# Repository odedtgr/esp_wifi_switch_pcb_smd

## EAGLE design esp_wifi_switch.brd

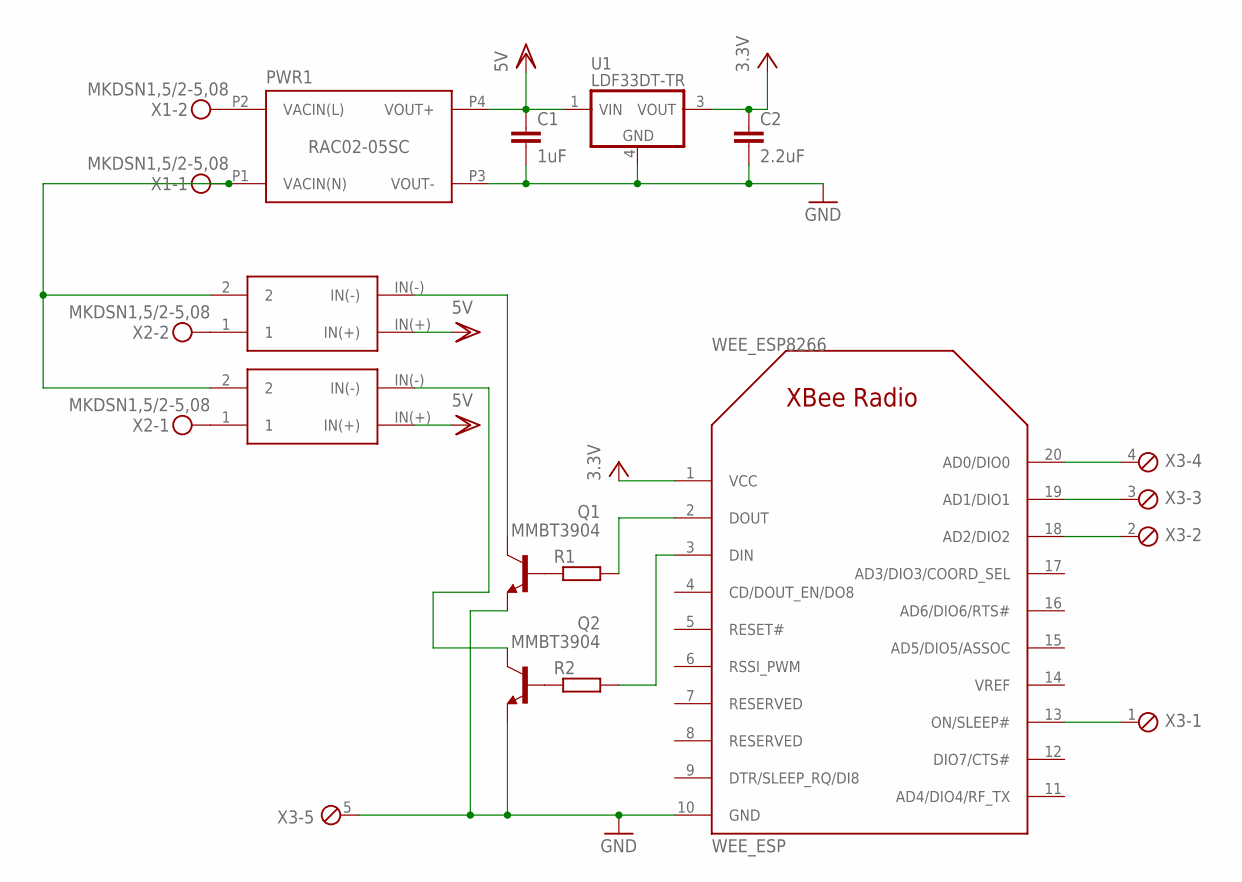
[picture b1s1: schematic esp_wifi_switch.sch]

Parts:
C1: 1uF; C3225
C2: 2.2uF; C3225
PWR1: RAC02-05SC; LOW_PROFILE_POWER_MODULE
Q1, Q2: MMBT3904; SOT23-BEC
R1, R2: R-EU_M1206; M1206
U1: LDF33DT-TR; DPAK-3
U$1, U$2: G3MB
WEE_ESP8266: WEE_ESP; XBEE
X1, X2: MKDSN1,5/2-5,08
X3: MPT5; 5POL254

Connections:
GND: C1.2, C2.2, PWR1.P3 (VOUT-), Q1.E, Q2.E, U1.4 (GND), WEE_ESP8266.10 (GND), X3.5
unnamed: PWR1.P2 (VACIN(L)), X1.2
unnamed: PWR1.P1 (VACIN(N)), U$1.2, U$2.2, X1.1
unnamed: U$1.1, X2.2
unnamed: U$2.1, X2.1
unnamed: WEE_ESP8266.13 (ON/SLEEP#), X3.1
unnamed: WEE_ESP8266.18 (AD2/DIO2), X3.2
unnamed: WEE_ESP8266.19 (AD1/DIO1), X3.3
unnamed: WEE_ESP8266.20 (AD0/DIO0), X3.4
unnamed: Q1.B, R1.1
unnamed: Q2.B, R2.1
unnamed: Q1.C, U$1.IN(-)
unnamed: R1.2, WEE_ESP8266.2 (DOUT)
unnamed: R2.2, WEE_ESP8266.3 (DIN)
unnamed: Q2.C, U$2.IN(-)
VDD: C1.1, PWR1.P4 (VOUT+), U1.1 (VIN), U$1.IN(+), U$2.IN(+)
VOUT: C2.1, U1.3 (VOUT), WEE_ESP8266.1 (VCC)

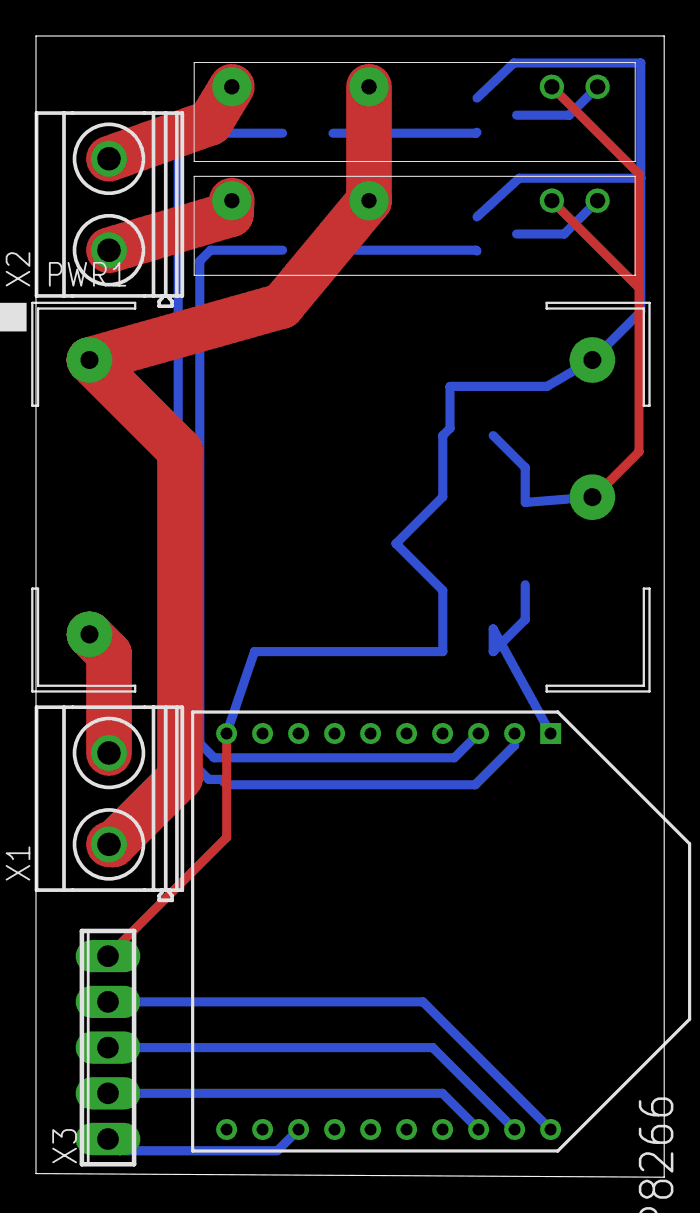
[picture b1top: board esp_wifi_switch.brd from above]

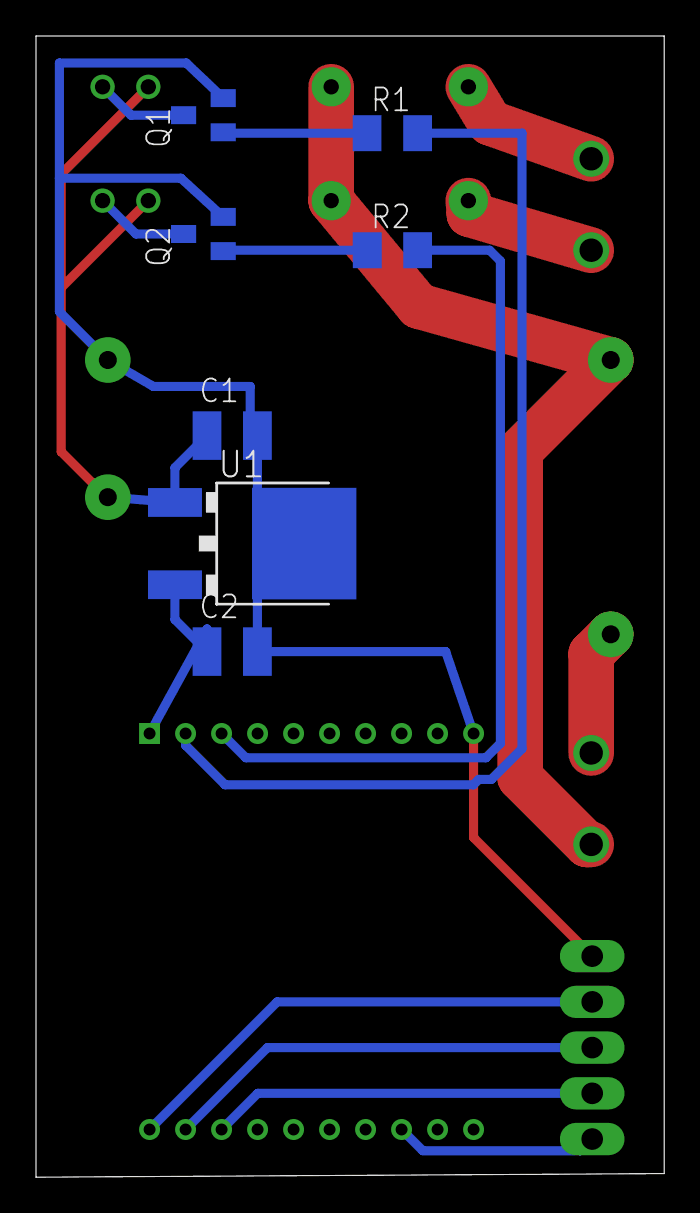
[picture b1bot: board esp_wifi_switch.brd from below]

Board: 2 copper layers, 34.9 x 63.4 mm, 14 parts (7 on the bottom side), 17 nets.

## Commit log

2018-01-14 :tada: Added .gitattributes & .gitignore files
